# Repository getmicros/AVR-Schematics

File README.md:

AVR-Schematics
==============

AVR schematics

This is a collection of AVR schematics and board designs in Eagle

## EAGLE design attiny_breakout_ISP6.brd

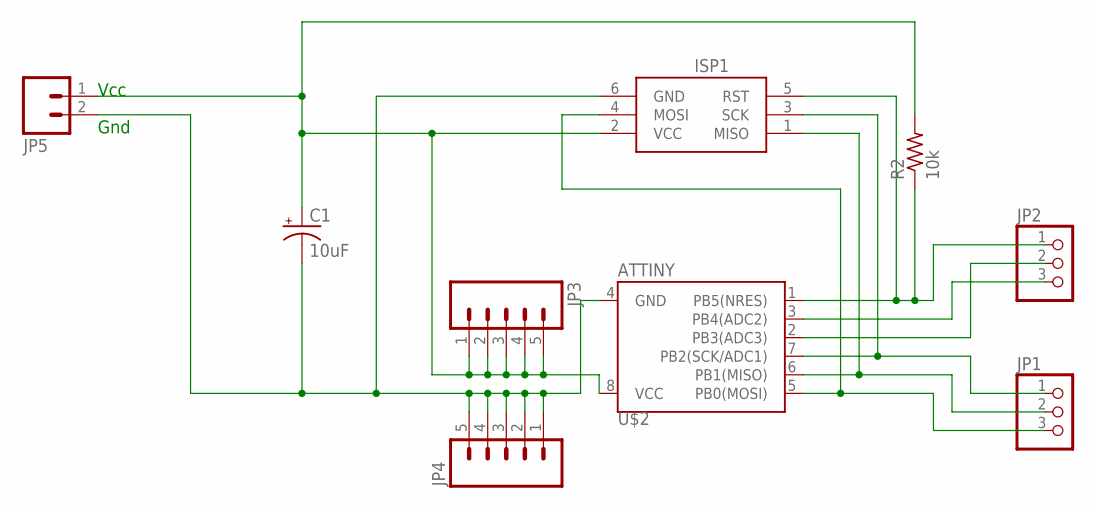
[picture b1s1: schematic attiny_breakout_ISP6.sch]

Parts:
C1: 10uF; CPOL-RADIAL-10UF-25V
ISP1: AVRISP-6; AVRISP
JP1, JP2: PINHD-1X3; 1X03
JP3, JP4: M05PTH; 1X05
JP5: M02PTH; 1X02
R2: 10k; 0207/12
U$2: ATTINY; DIP08

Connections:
unnamed: ISP1.4 (MOSI), JP1.3, U$2.5 (PB0(MOSI))
unnamed: ISP1.1 (MISO), JP1.2, U$2.6 (PB1(MISO))
unnamed: ISP1.5 (RST), JP2.1, R2.1, U$2.1 (PB5(NRES))
unnamed: ISP1.3 (SCK), JP1.1, U$2.7 (PB2(SCK/ADC1))
unnamed: JP2.2, U$2.2 (PB3(ADC3))
unnamed: JP2.3, U$2.3 (PB4(ADC2))
unnamed: C1.2 (-), ISP1.6 (GND), JP4.1, JP4.2, JP4.3, JP4.4, JP4.5, JP5.2, U$2.4 (GND)
unnamed: C1.1 (+), ISP1.2 (VCC), JP3.1, JP3.2, JP3.3, JP3.4, JP3.5, JP5.1, R2.2, U$2.8 (VCC)

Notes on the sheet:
Vcc
Gnd

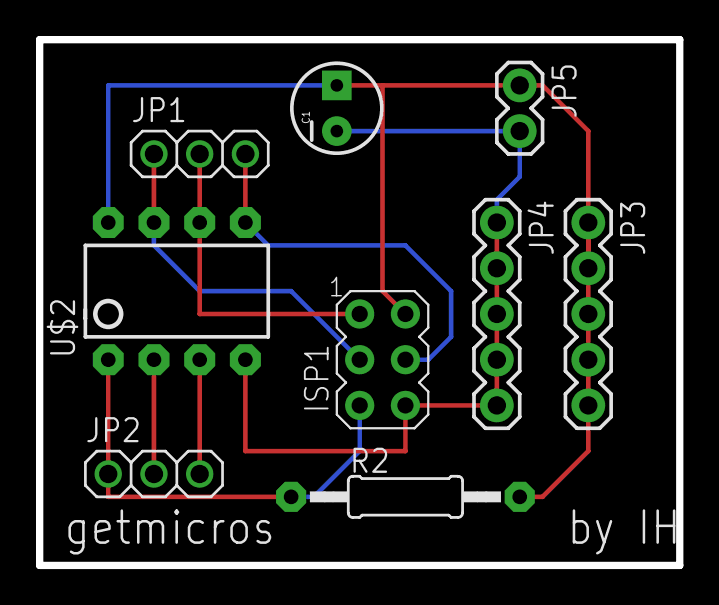
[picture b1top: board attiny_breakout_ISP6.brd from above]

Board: 2 copper layers, 35.6 x 29.2 mm, 9 parts (0 on the bottom side), 8 nets.

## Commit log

2014-12-13 :tada: Added .gitattributes & .gitignore files
2014-12-13 Design attempt 1
    Design attempt 1

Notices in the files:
parts and their libraries:
SparkFun-Connectors: Licensing: CC v3.0 Share-Alike You are welcome to use this library for commercial purposes.
